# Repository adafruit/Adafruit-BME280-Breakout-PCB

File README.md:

## Adafruit BME280 Breakout PCB

<a href="http://www.adafruit.com/products/2652"><br/>
Click here to purchase one from the Adafruit shop</a>

PCB files for the Adafruit BME280 Breakout. Format is EagleCAD schematic and board layout
* https://www.adafruit.com/product/2652

### Description

Bosch has stepped up their game with their new BME280 sensor, an environmental sensor with temperature, barometric pressure and humidity! This sensor is great for all sorts of weather/environmental sensing and can even be used in both I2C and SPI!

This precision sensor from Bosch is the best low-cost sensing solution for measuring humidity with ±3% accuracy, barometric pressure with ±1 hPa absolute accuraccy, and temperature with ±1.0°C accuracy. Because pressure changes with altitude, and the pressure measurements are so good, you can also use it as an altimeter with  ±1 meter or better accuracy!

The BME280 is the next-generation of sensors from Bosch, and is the upgrade to the BMP085/BMP180/BMP183 - with a low altitude noise of 0.25m and the same fast conversion time. It has the same specifications, but can use either I2C or SPI. For simple easy wiring, go with I2C. If you want to connect a bunch of sensors without worrying about I2C address collisions, go with SPI.

### License

Adafruit invests time and resources providing this open source design, please support Adafruit and open-source hardware by purchasing products from [Adafruit](https://www.adafruit.com)!

Designed by Limor Fried/Ladyada for Adafruit Industries.

Creative Commons Attribution/Share-Alike, all text above must be included in any redistribution. See license.txt for additional details.

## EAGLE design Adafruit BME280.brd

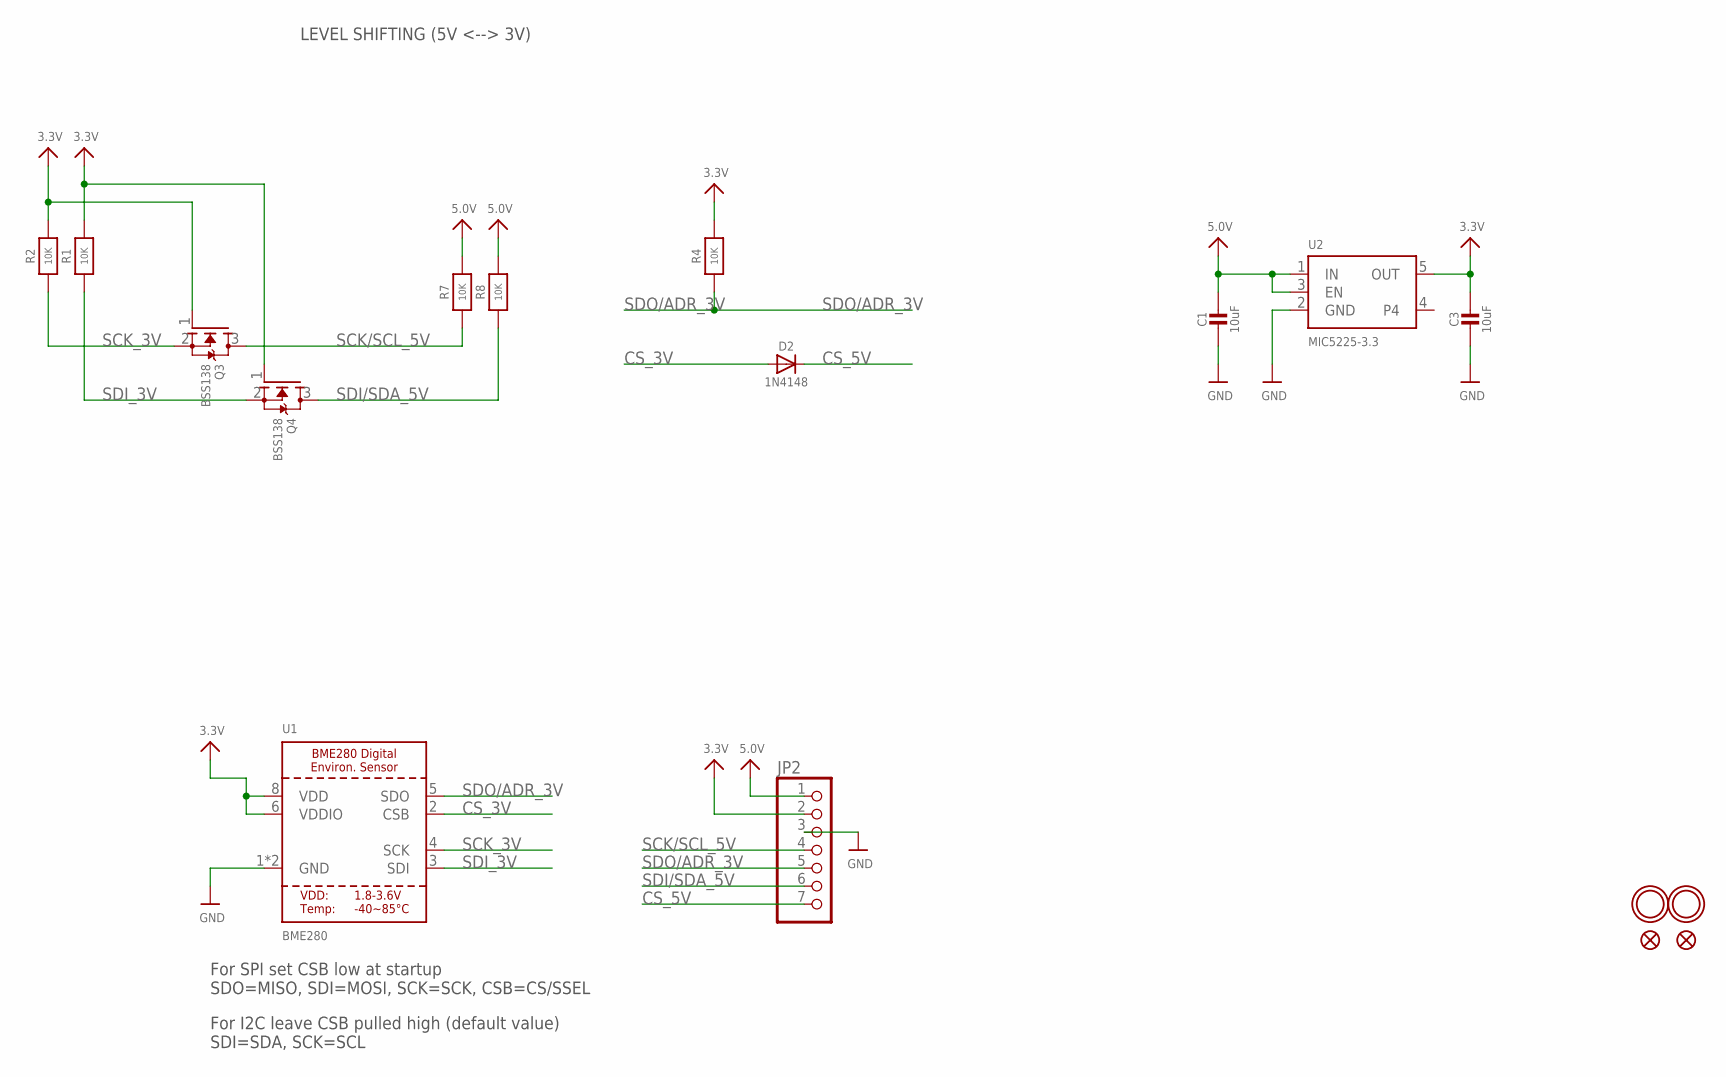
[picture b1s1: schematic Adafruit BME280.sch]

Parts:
C1, C3: 10uF; 0805-NO
D2: 1N4148; SOD-323
JP2: HEADER-1X770MIL; 1X07_ROUND_70
Q3, Q4: BSS138; SOT23-WIDE
R1, R2, R7, R8: 10K; 0805-NO
R4: 10K; _0805MP
U1: BME280
U2: MIC5225-3.3; SOT23-5
U$5, U$15: FIDUCIAL""; FIDUCIAL_1MM
U$7, U$8: MOUNTINGHOLE2.0; MOUNTINGHOLE_2.0_PLATED

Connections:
3.3V: C3.1, JP2.2, Q3.1 (G), Q4.1 (G), R1.2, R2.2, R4.2, U1.6 (VDDIO), U1.8 (VDD), U2.5 (OUT)
5.0V: C1.1, JP2.1, R7.2, R8.2, U2.1 (IN), U2.3 (EN)
CS_3V: D2.A, U1.2 (CSB)
CS_5V: D2.C, JP2.7
GND: C1.2, C3.2, JP2.3, U1.1 (GND), U1.7 (GND), U2.2 (GND)
SCK/SCL_5V: JP2.4, Q3.3 (D), R7.1
SCK_3V: Q3.2 (S), R2.1, U1.4 (SCK)
SDI/SDA_5V: JP2.6, Q4.3 (D), R8.1
SDI_3V: Q4.2 (S), R1.1, U1.3 (SDI)
SDO/ADR_3V: JP2.5, R4.1, U1.5 (SDO)

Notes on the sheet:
For SPI set CSB low at startup SDO=MISO, SDI=MOSI, SCK=SCK, CSB=CS/SSEL
For I2C leave CSB pulled high (default value) SDI=SDA, SCK=SCL
LEVEL SHIFTING (5V <--> 3V)

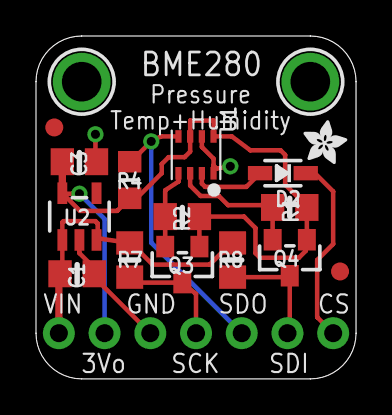
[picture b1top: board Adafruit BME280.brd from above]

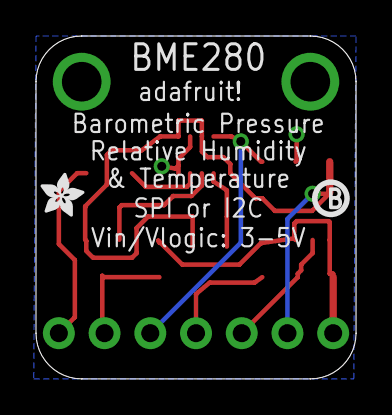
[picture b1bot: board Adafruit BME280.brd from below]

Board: 2 copper layers, 17.8 x 19.1 mm, 20 parts (2 on the bottom side), 10 nets.

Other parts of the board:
U$2, U$6: ADAFRUIT_2.5MM
U$20: PCBFEAT-REV-040

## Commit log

2016-09-27 init
